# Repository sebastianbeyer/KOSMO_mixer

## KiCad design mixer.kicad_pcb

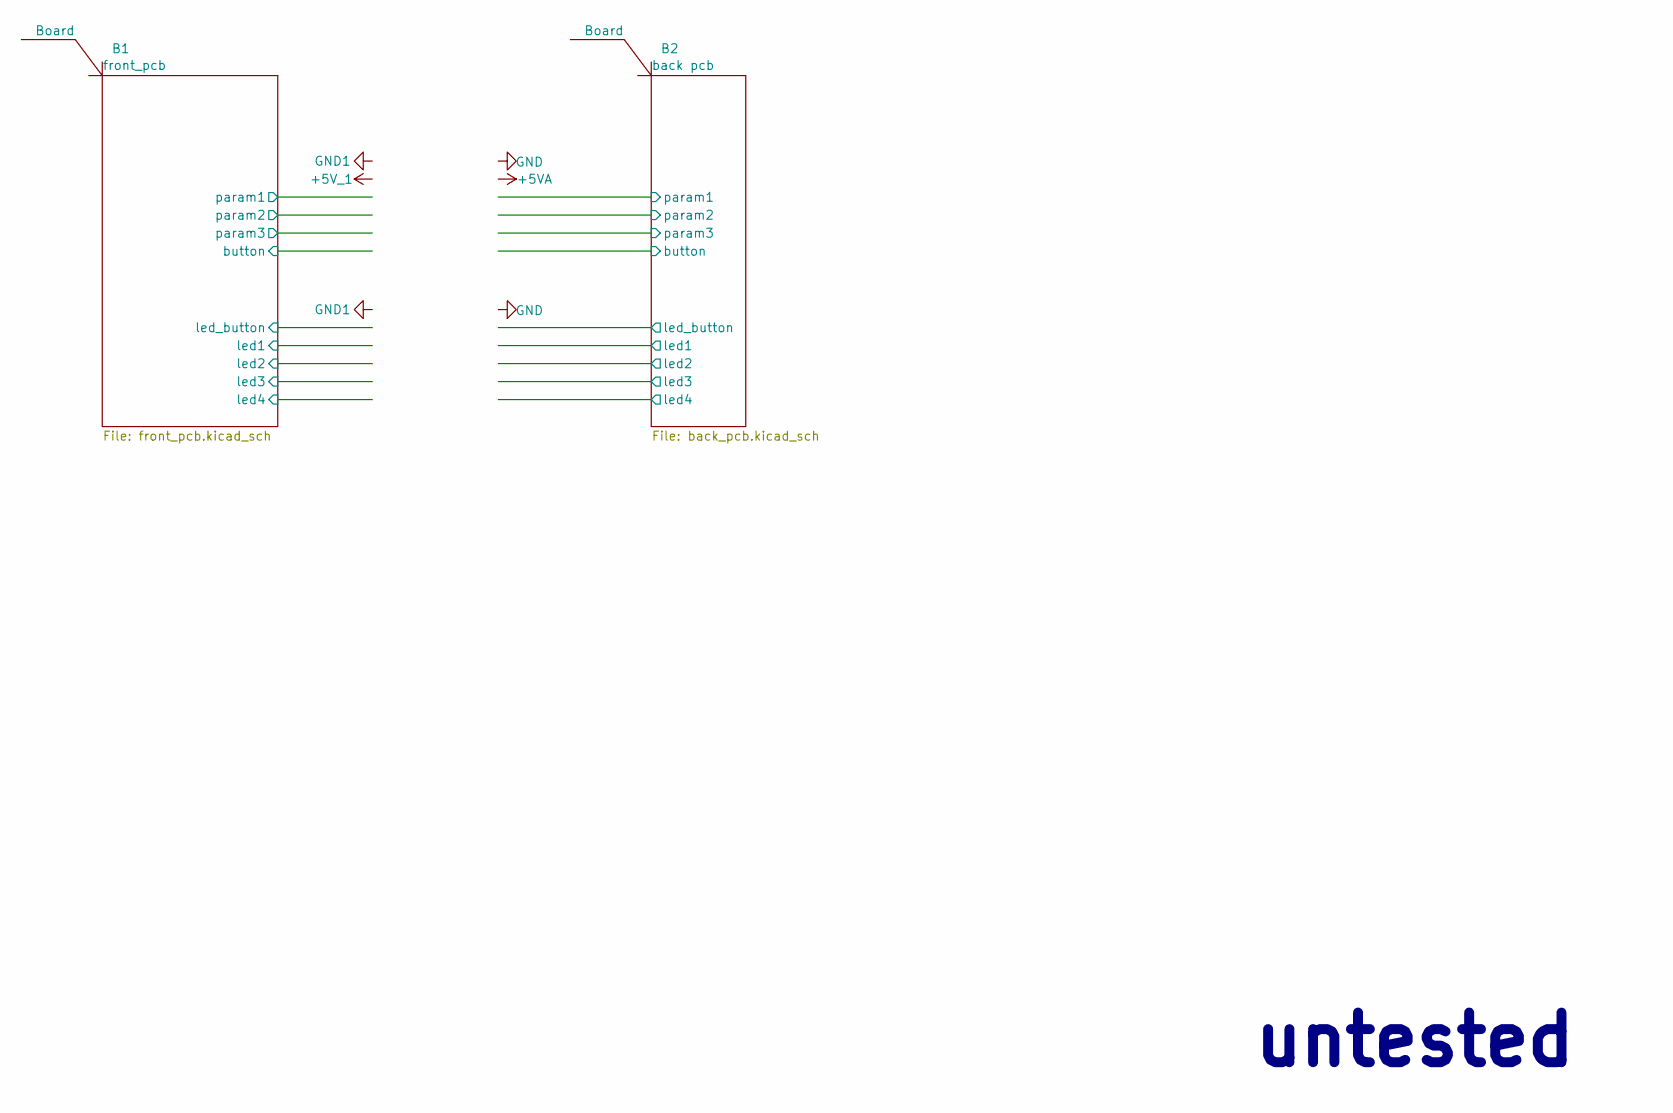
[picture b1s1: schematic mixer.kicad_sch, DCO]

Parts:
B1, B2: Board; Board_Marker

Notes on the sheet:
untested

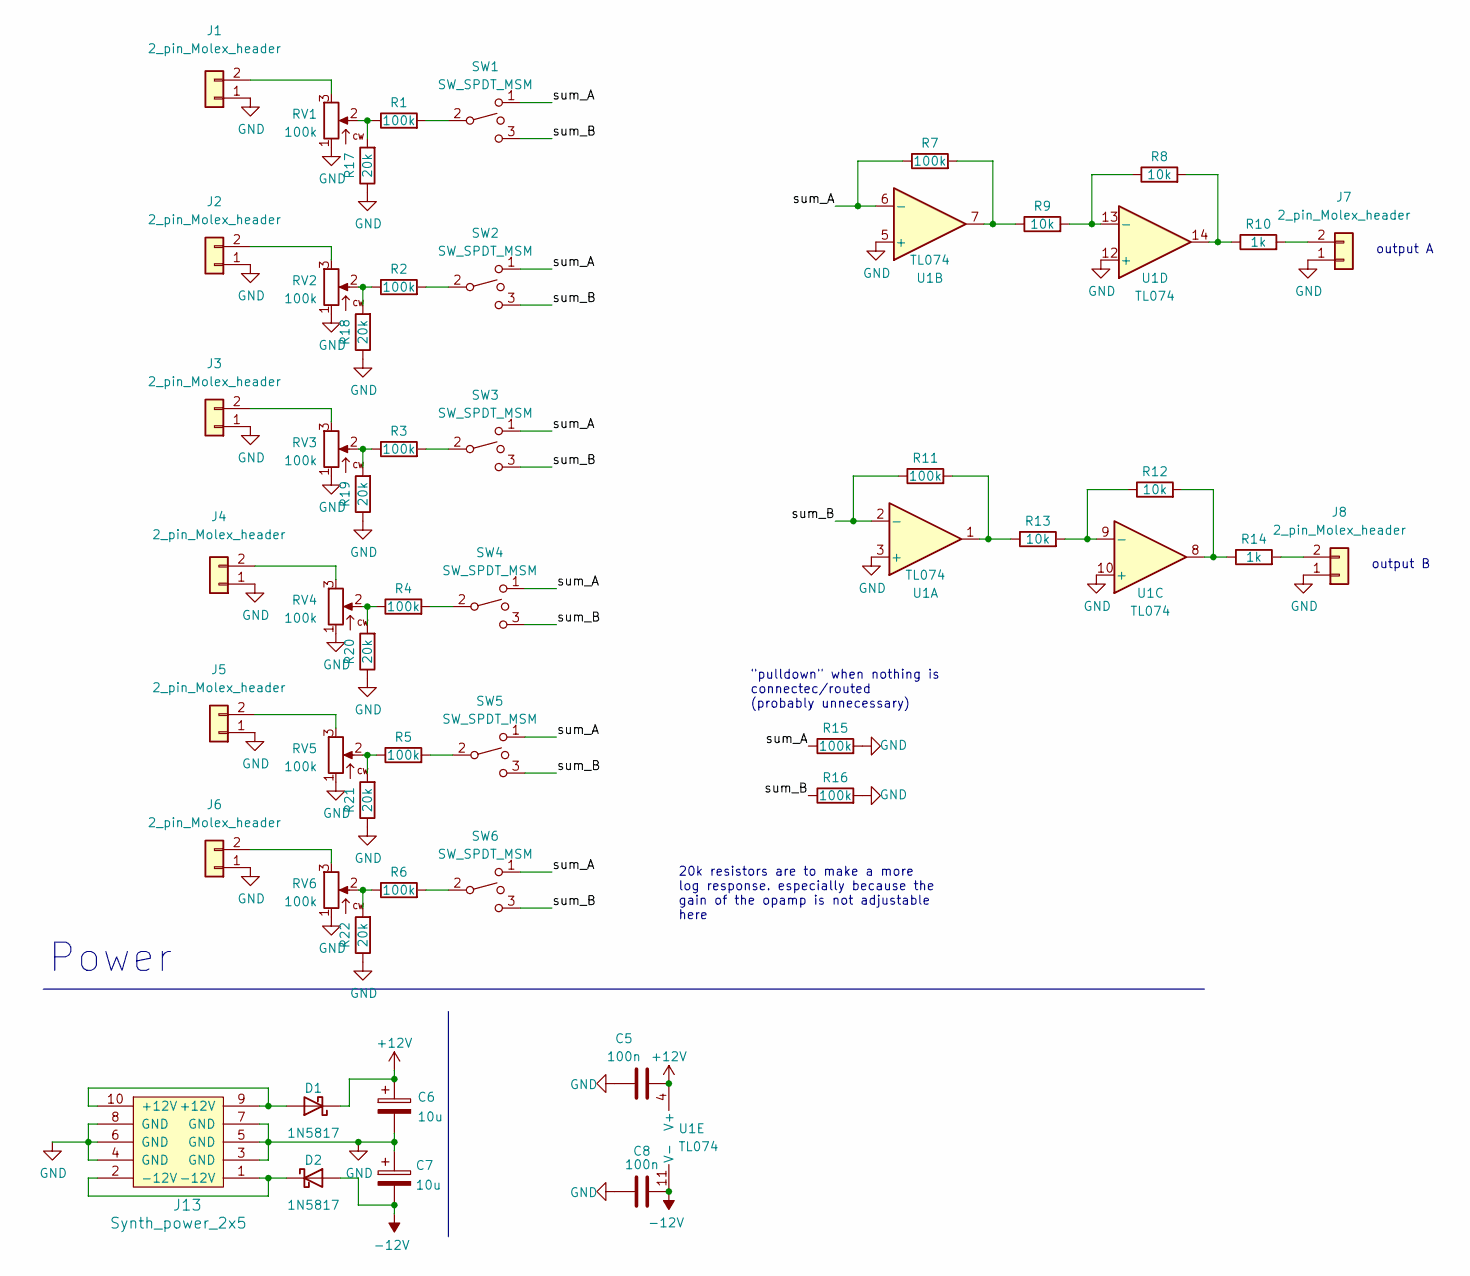
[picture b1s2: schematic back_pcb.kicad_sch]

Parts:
C5, C8: 100n; C_Disc_D3.0mm_W1.6mm_P2.50mm
C6, C7: 10u; CP_Radial_horizontalflat_D5mm_P2.50mm_H10mm_south
D1, D2: 1N5817; D_DO-41_SOD81_P10.16mm_Horizontal
J1, J2, J3, J4, J5, J6, J7, J8: 2_pin_Molex_header; Molex_KK-254_AE-6410-02A_1x02_P2.54mm_Vertical
J13: Synth_power_2x5; Power_Header
R1, R2, R3, R4, R5, R6, R7, R11, R15, R16: 100k; R_Axial_DIN0207_L6.3mm_D2.5mm_P2.54mm_Vertical
R8, R9, R12, R13: 10k; R_Axial_DIN0207_L6.3mm_D2.5mm_P2.54mm_Vertical
R10, R14: 1k; R_Axial_DIN0207_L6.3mm_D2.5mm_P2.54mm_Vertical
R17, R18, R19, R20, R21, R22: 20k; R_Axial_DIN0207_L6.3mm_D2.5mm_P2.54mm_Vertical
RV1, RV2, RV3, RV4, RV5, RV6: 100k; Potentiometer_Alpha_RD901F-40-00D_Single_Vertical_centered
SW1, SW2, SW3, SW4, SW5, SW6: SW_SPDT_MSM; SPDT-toggle-switch-1M-series
U1: TL074; DIP-14_W7.62mm_Socket_LongPads

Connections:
+12V: C5.2, C6.1, D1.1 (K), U1.4 (V+)
-12V: C7.2, C8.2, D2.2 (A), U1.11 (V-)
/back pcb/sum_A: R7.1, R15.1, SW1.1, SW2.1, SW3.1, SW4.1, SW5.1, SW6.1, U1.6 (-)
/back pcb/sum_B: R11.1, R16.1, SW1.3, SW2.3, SW3.3, SW4.3, SW5.3, SW6.3, U1.2 (-)
GND: C5.1, C6.2, C7.1, C8.1, J1.1, J2.1, J3.1, J4.1, J5.1, J6.1, J7.1, J8.1, J13.3 (GND), J13.4 (GND), J13.5 (GND), J13.6 (GND), J13.7 (GND), J13.8 (GND), R15.2, R16.2, R17.1, R18.1, R19.1, R20.1, R21.1, R22.1, RV1.1, RV2.1, RV3.1, RV4.1, RV5.1, RV6.1, U1.3 (+), U1.5 (+), U1.10 (+), U1.12 (+)
unnamed: D1.2 (A), J13.9 (+12V), J13.10 (+12V)
unnamed: D2.1 (K), J13.1 (-12V), J13.2 (-12V)
unnamed: J1.2, RV1.3
unnamed: J2.2, RV2.3
unnamed: J3.2, RV3.3
unnamed: J4.2, RV4.3
unnamed: J5.2, RV5.3
unnamed: J6.2, RV6.3
unnamed: J7.2, R10.2
unnamed: J8.2, R14.2
unnamed: R1.1, R17.2, RV1.2
unnamed: R1.2, SW1.2
unnamed: R2.1, R18.2, RV2.2
unnamed: R2.2, SW2.2
unnamed: R3.1, R19.2, RV3.2
unnamed: R3.2, SW3.2
unnamed: R4.1, R20.2, RV4.2
unnamed: R4.2, SW4.2
unnamed: R5.1, R21.2, RV5.2
unnamed: R5.2, SW5.2
unnamed: R6.1, R22.2, RV6.2
unnamed: R6.2, SW6.2
unnamed: R7.2, R9.1, U1.7
unnamed: R8.1, R9.2, U1.13 (-)
unnamed: R8.2, R10.1, U1.14
unnamed: R11.2, R13.1, U1.1
unnamed: R12.1, R13.2, U1.9 (-)
unnamed: R12.2, R14.1, U1.8

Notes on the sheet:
20k resistors are to make a more log response. especially because the gain of the opamp is not adjustable here
output A
output B
Power
"pulldown" when nothing is connectec/routed (probably unnecessary)

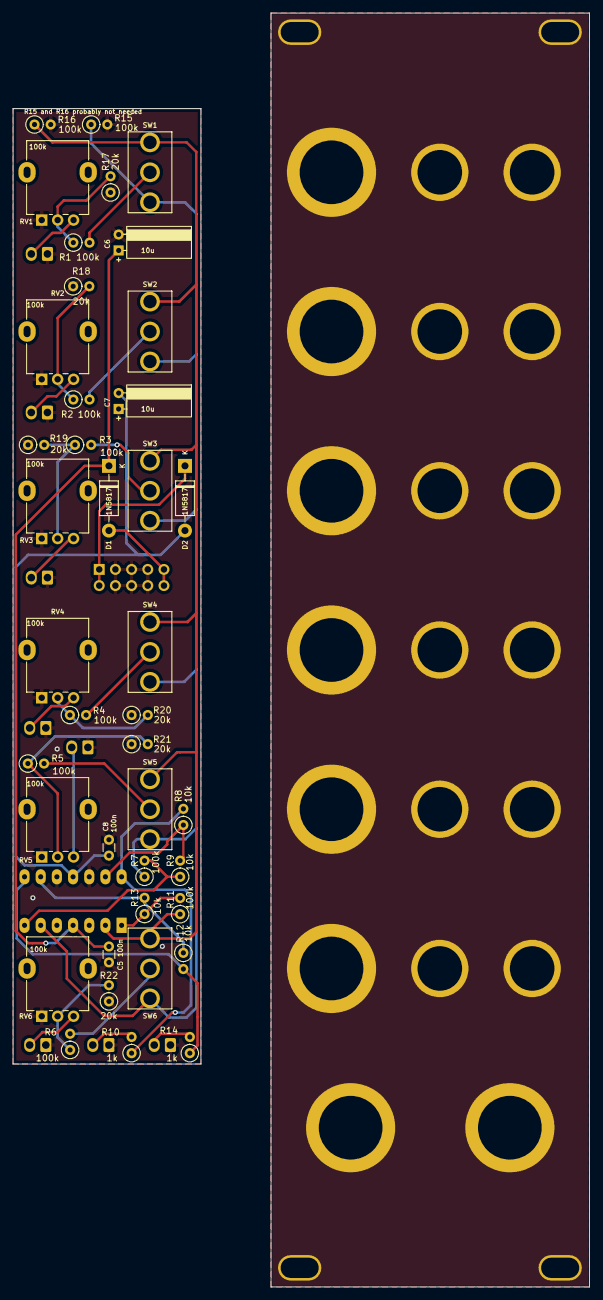
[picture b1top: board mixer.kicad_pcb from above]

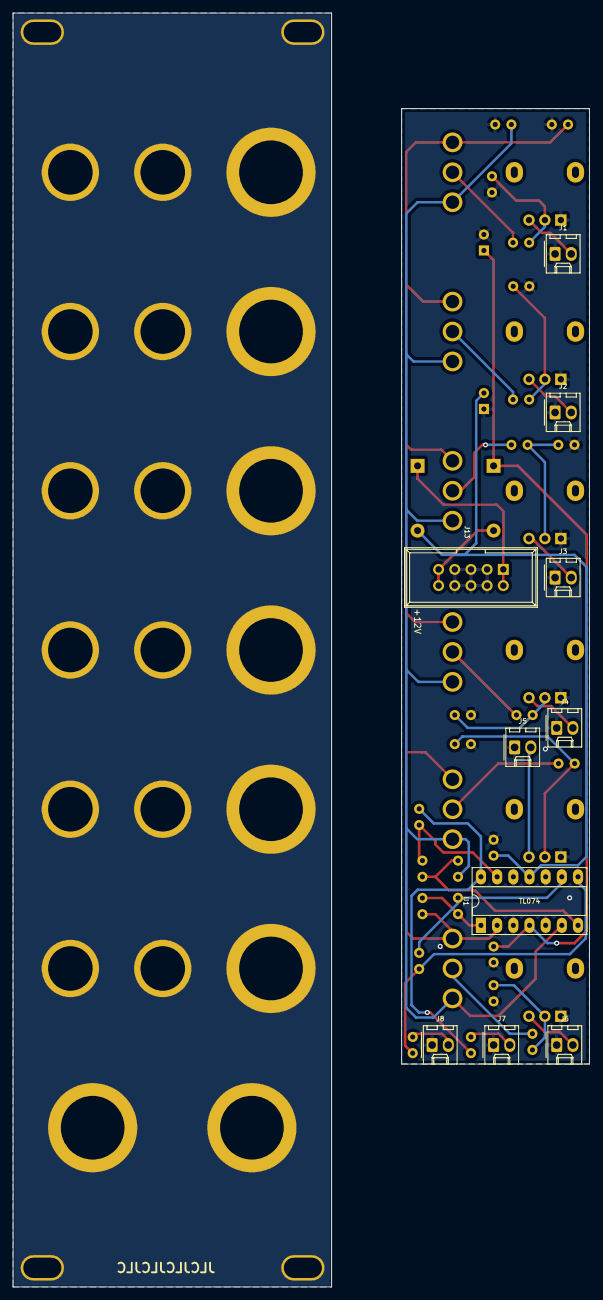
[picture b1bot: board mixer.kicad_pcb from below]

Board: 2 copper layers, 90.5 x 200.0 mm, 52 parts (10 on the bottom side), 33 nets.

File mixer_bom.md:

# mixer.kicad_sch BOM

Tue 22 Nov 2022 11:52:34 CET

Generated from schematic by Eeschema 6.0.8-f2edbf62ab~116~ubuntu22.04.1

**Component Count:** 50

| Refs | Qty | Component | Description | Vendor | SKU |
| ----- | --- | ---- | ----------- | ---- | ---- |
| C5, C8 | 2 | 100n | Unpolarized capacitor |  |  |
| C6, C7 | 2 | 10u | Polarized capacitor | Tayda |  |
| D1, D2 | 2 | 1N5817 | Schottky Barrier Rectifier Diode, DO-41 | Tayda | A-159 |
| J1, J2, J3, J4, J5, J6, J7, J8 | 8 | 2_pin_Molex_header | KK254 Molex header | Tayda | A-804 |
| J13 | 1 | Synth_power_2x5 | Pin header 2.54 mm 2x5 | Tayda | A-2939 |
| R1, R2, R3, R4, R5, R6, R7, R11, R15, R16 | 10 | 100k | Resistor | Tayda |  |
| R8, R9, R12, R13 | 4 | 10k | Resistor | Tayda |  |
| R10, R14 | 2 | 1k | Resistor | Tayda |  |
| R17, R18, R19, R20, R21, R22 | 6 | 20k | Resistor | Tayda |  |
| RV1, RV2, RV3, RV4, RV5, RV6 | 6 | 100k | Potentiometer | Tayda |  |
| SW1, SW2, SW3, SW4, SW5, SW6 | 6 | SW_SPDT_MSM | Switch, single pole double throw, center OFF position | Tayda | A-3187 |
| U1 | 1 | TL074 | Quad operational amplifier, DIP-14 | Tayda | A-1138 |

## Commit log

2022-11-15 initial
2022-11-22 add BOM
